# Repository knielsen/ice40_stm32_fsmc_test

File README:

Small test of fast communication between STM32F4 and ICE40 using the STM32 FSMC.

Pinout for the FSMC (this for plugged into the J3 slot):

  func  STM32  ICE40
  A0    PF0    R4
  A1    PF1    R3
  D0	PD14   N10
  D1	PD15   M11
  D2	PD0    T16
  NE2	PG9    N12
  NOE	PD4    T13
  NWE	PD5    P13

The external clock for the ICE40 is on J3. A test pin PB11 on the
STM32F4 is connected to R16 on the ICE40. A serial Tx out from STM32
can be connected from PB10 on the STM32F4 board to T15 on the ICE40
(will be proxied to the FTDI on the ICE40 breakout board).

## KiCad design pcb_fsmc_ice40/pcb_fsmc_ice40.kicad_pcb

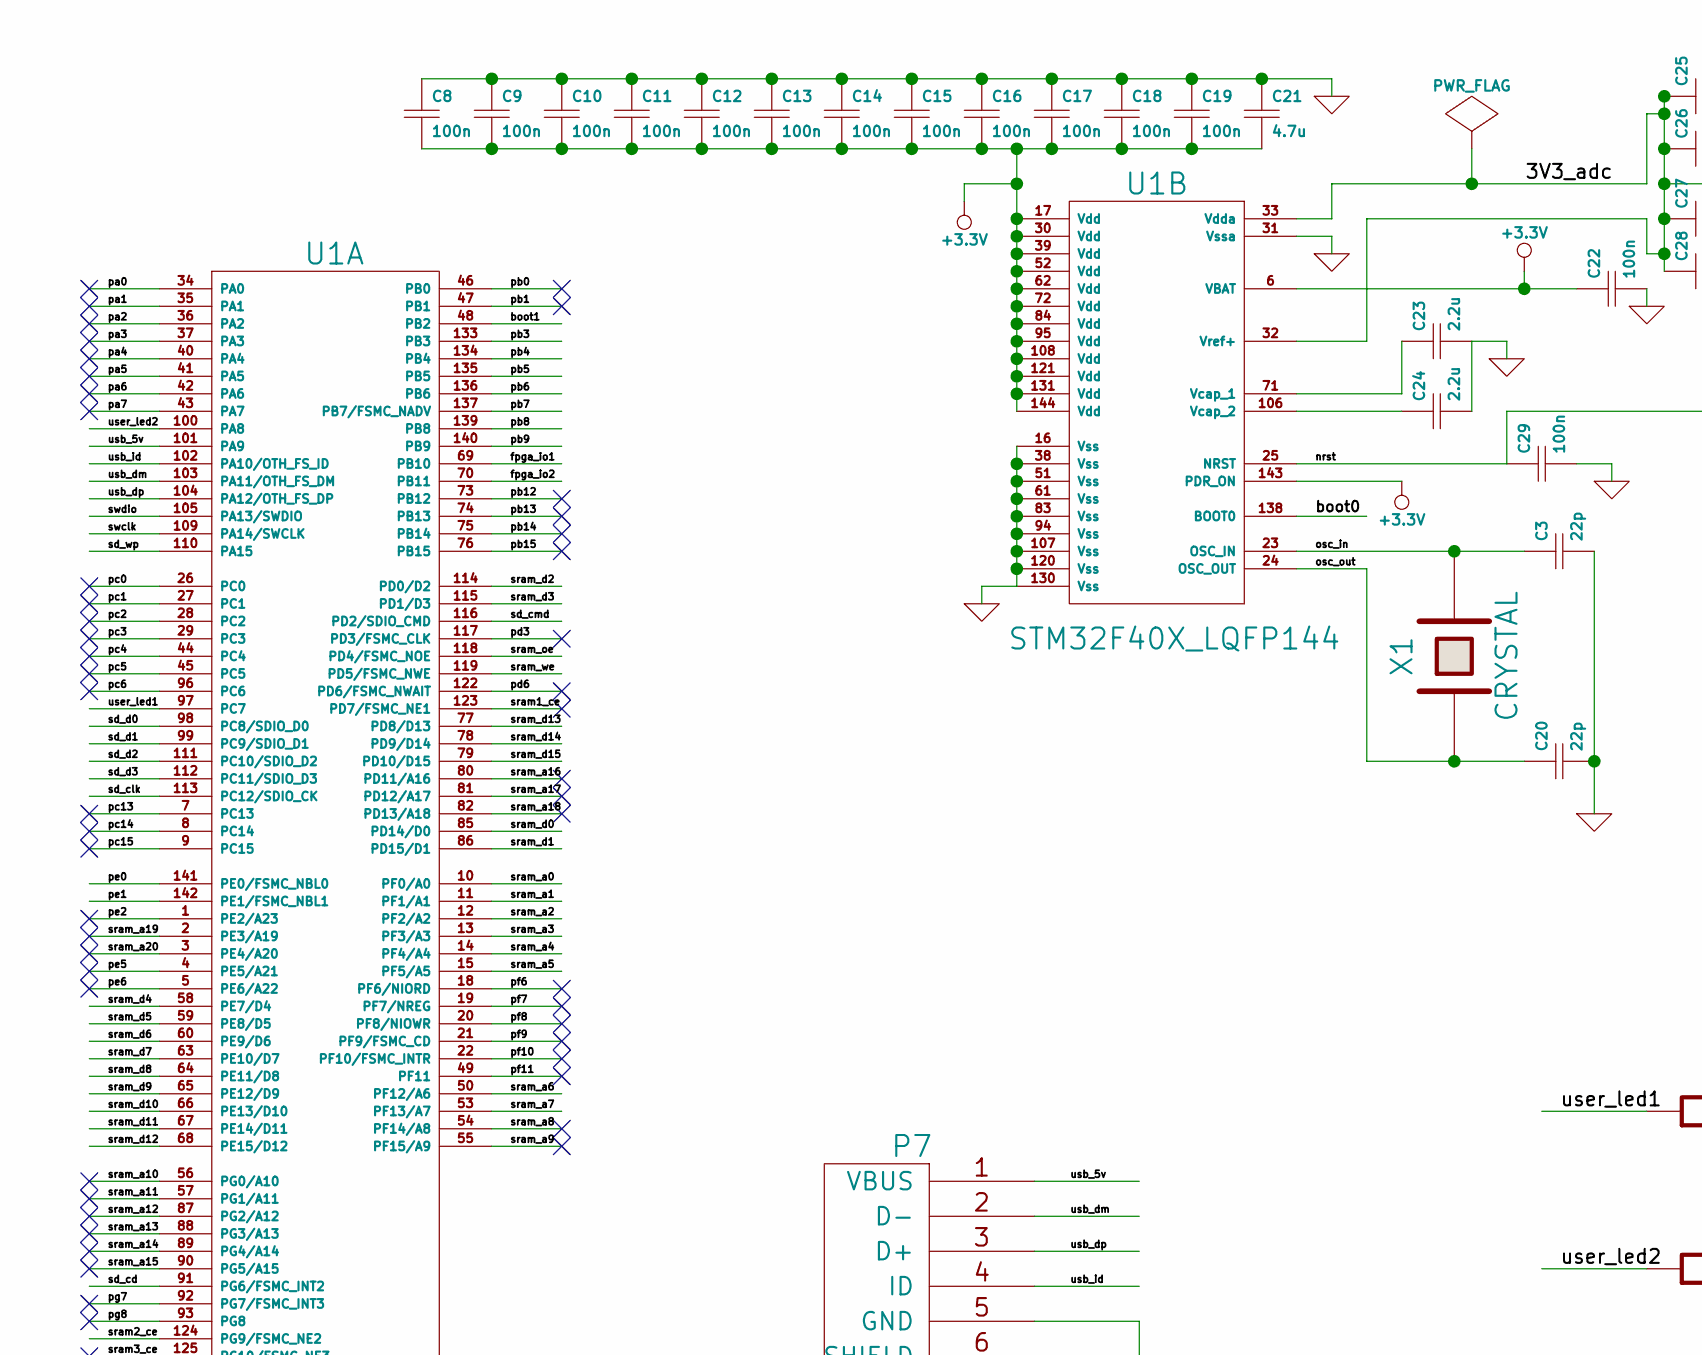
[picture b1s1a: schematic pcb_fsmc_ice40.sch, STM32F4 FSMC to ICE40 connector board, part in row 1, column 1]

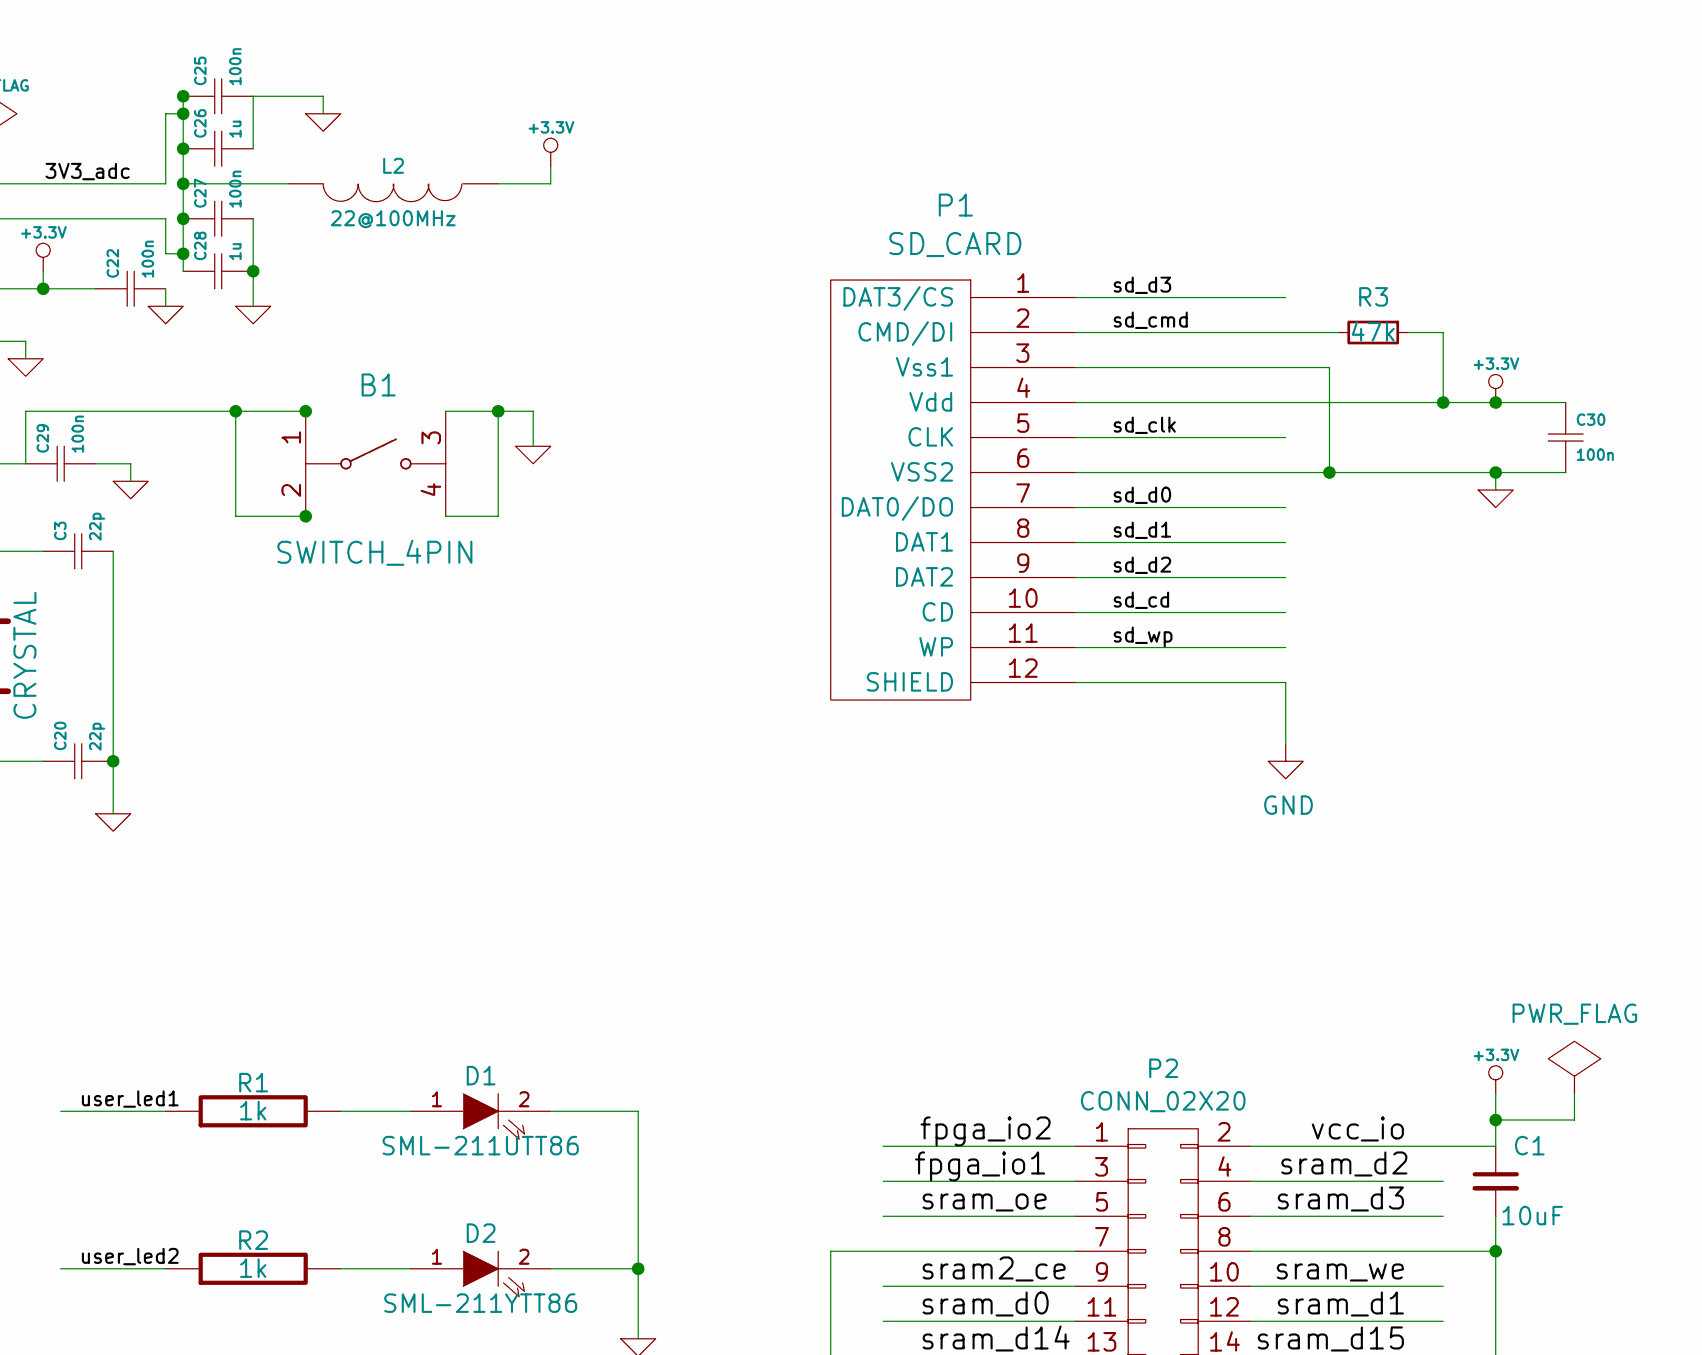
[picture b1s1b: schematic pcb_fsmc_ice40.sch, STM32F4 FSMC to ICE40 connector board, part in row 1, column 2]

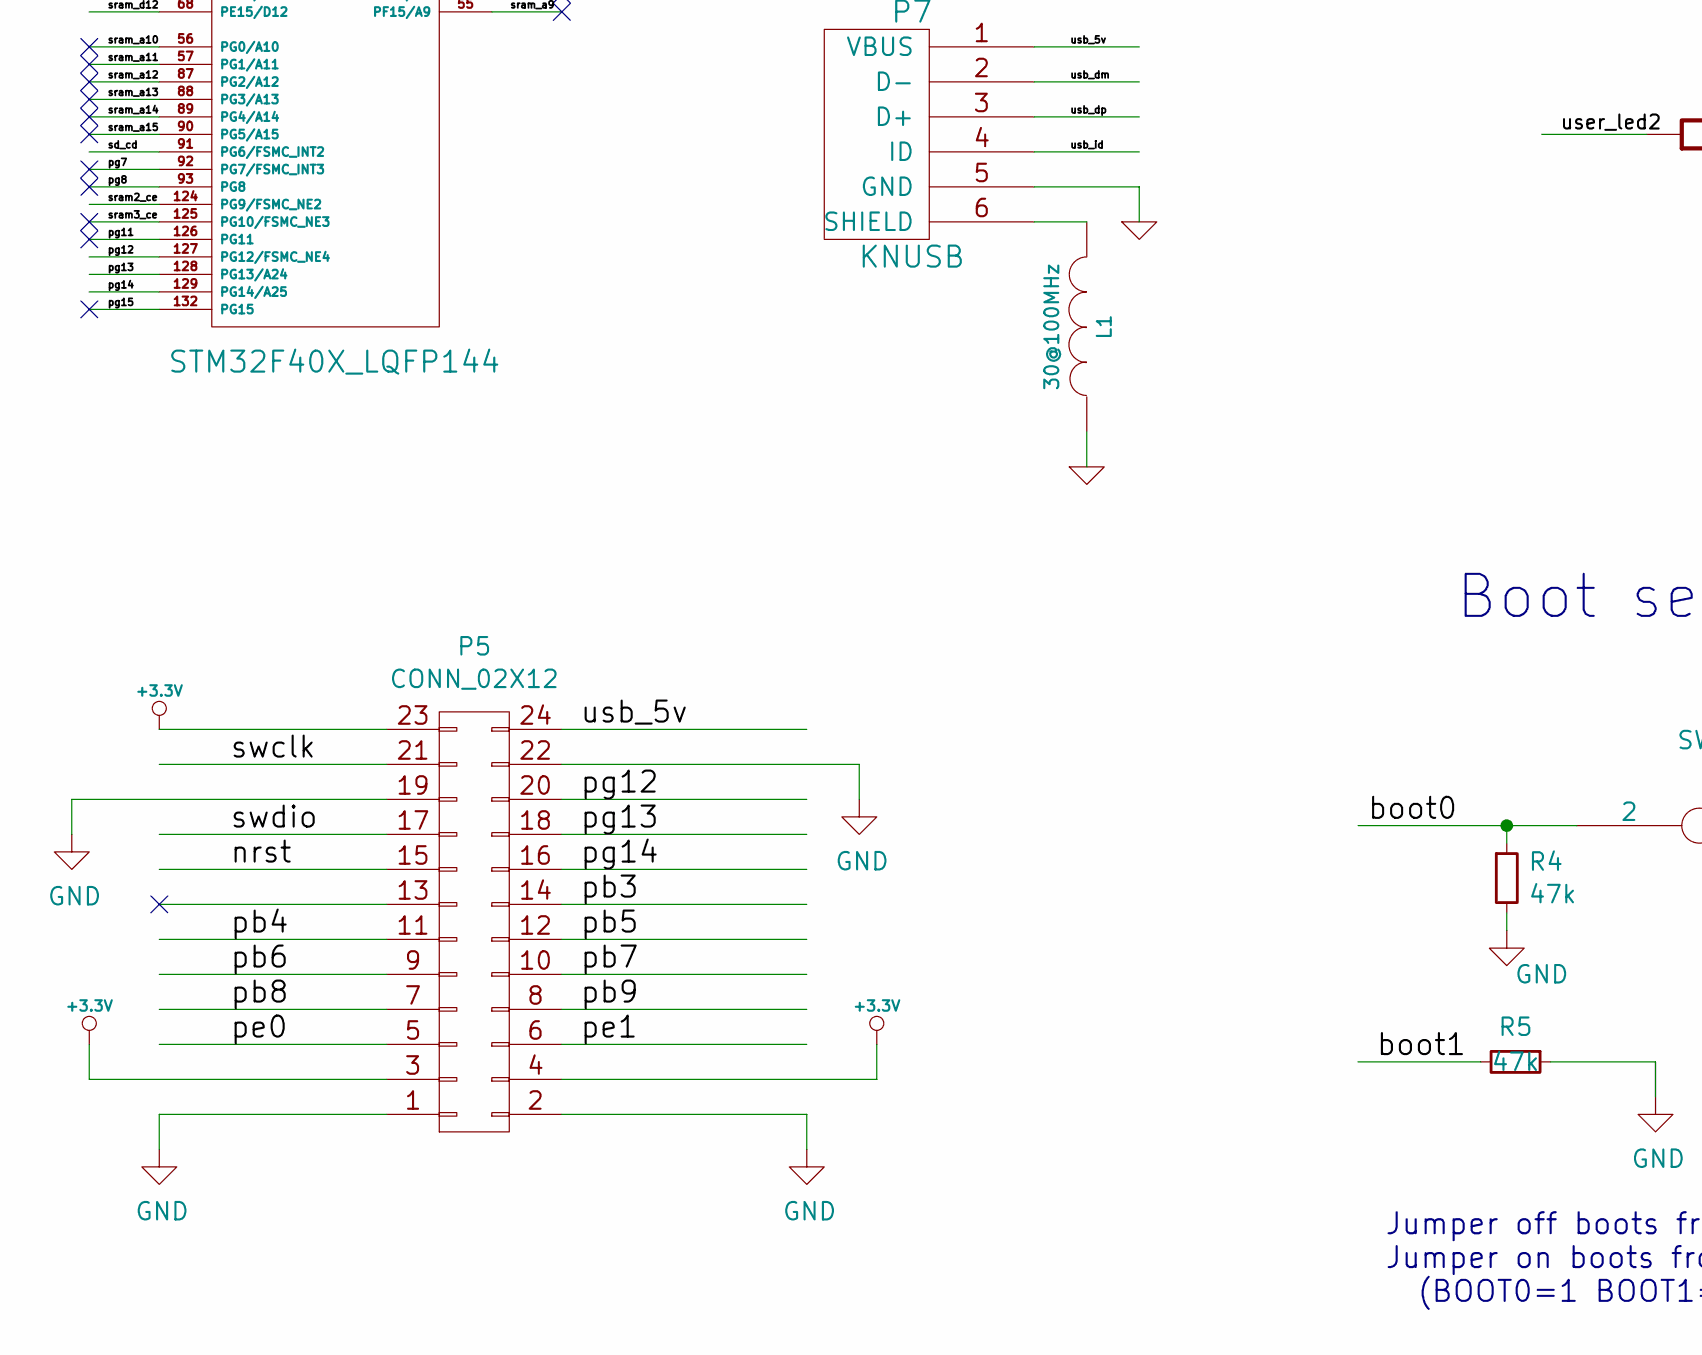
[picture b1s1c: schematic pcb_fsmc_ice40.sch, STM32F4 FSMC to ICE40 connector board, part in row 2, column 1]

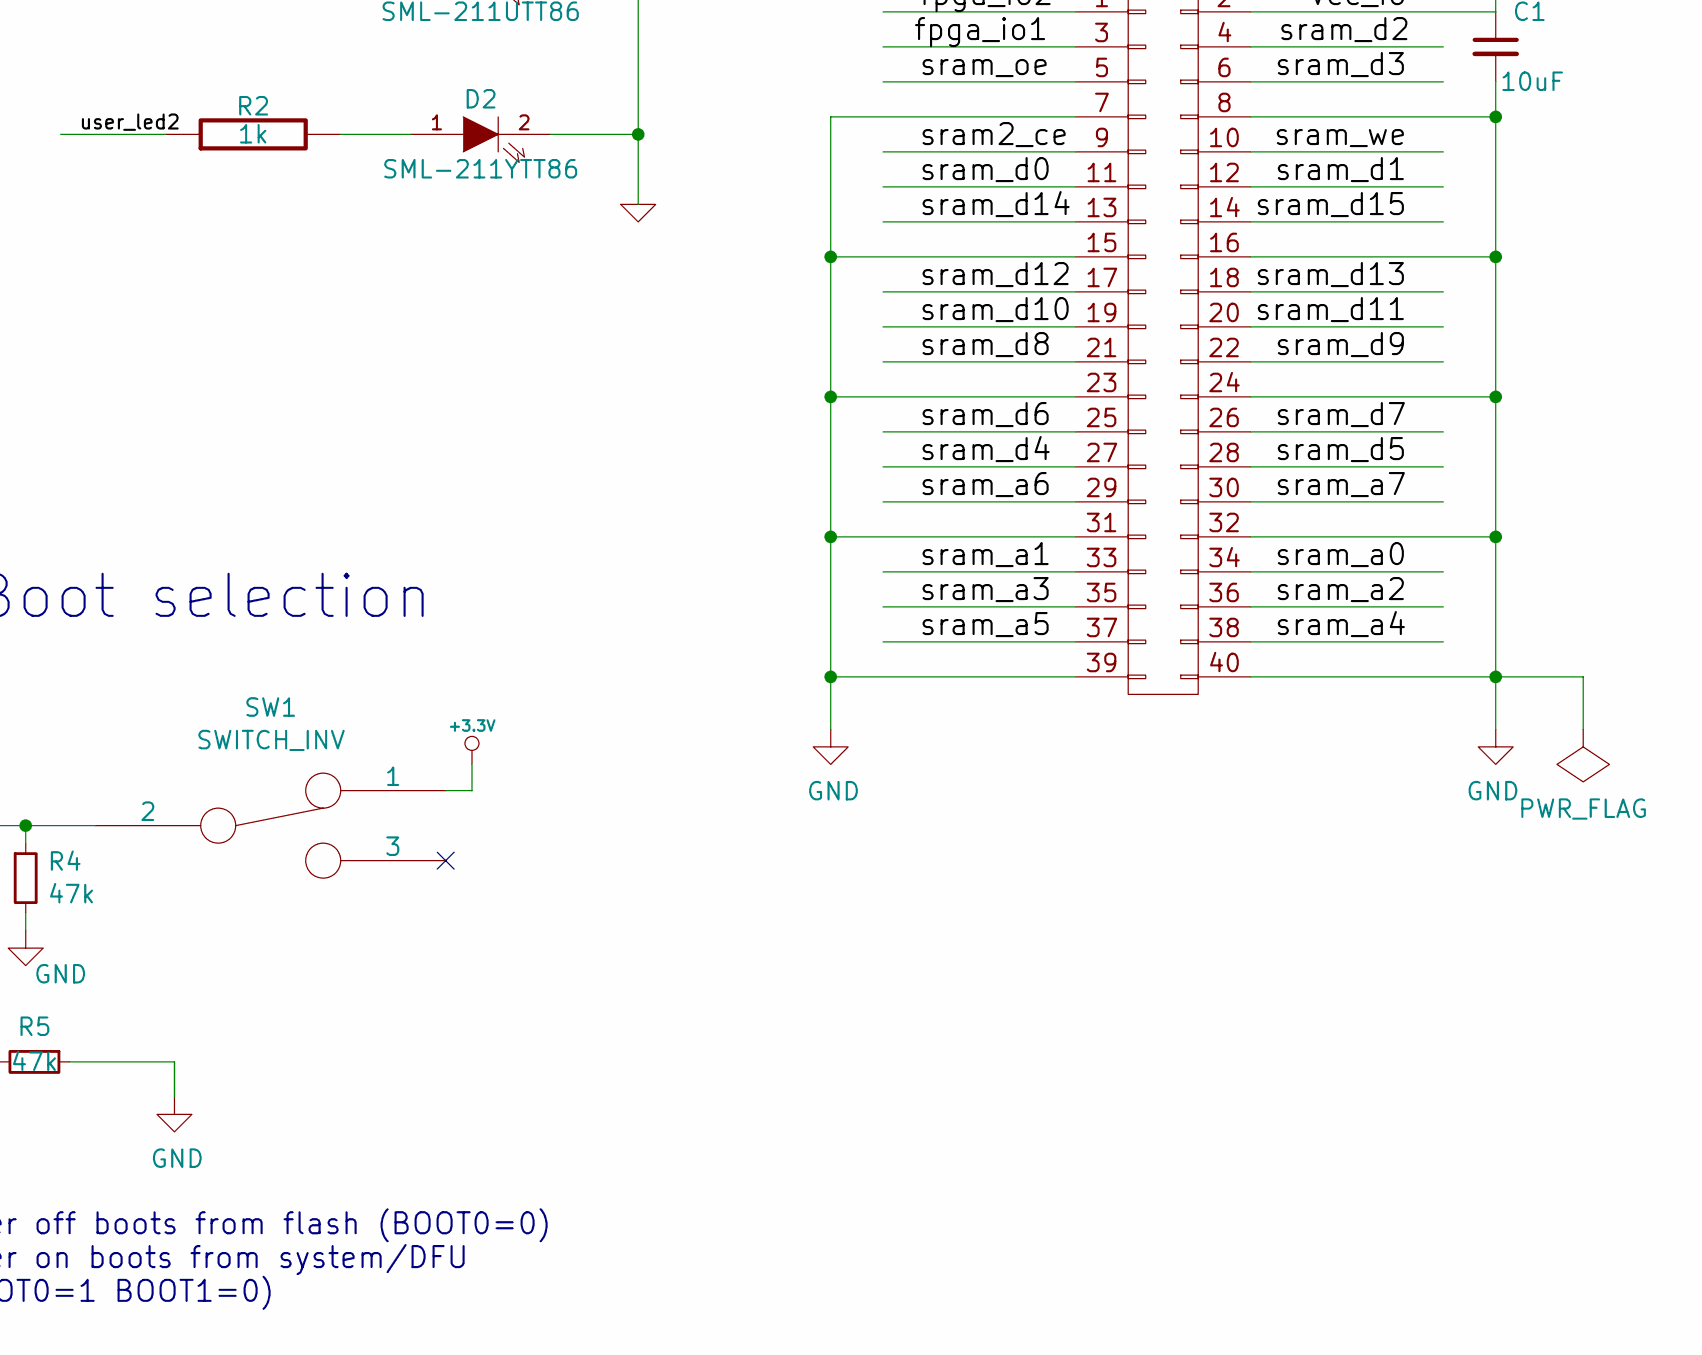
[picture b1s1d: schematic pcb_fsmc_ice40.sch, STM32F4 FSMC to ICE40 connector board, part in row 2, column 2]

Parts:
B1: SWITCH_4PIN; pushbutton_EVQ_PSR02K
C1: 10uF; C_0805
C3, C20: 22p; C_0603
C8, C9, C10, C11, C12, C13, C14, C15, C16, C17, C18, C19, C22, C25, C27, C29, C30: 100n; C_0603
C21: 4.7u; C_0603
C23, C24: 2.2u; C_0603
C26, C28: 1u; C_0603
D1: SML-211UTT86; LED_0603
D2: SML-211YTT86; LED_0603
L1: 30@100MHz; C_0603
L2: 22@100MHz; C_0603
P1: SD_CARD; SD_CARD_10100
P2: CONN_02X20; ice40_vert_conn
P5: CONN_02X12; ice40_top_conn_12
P7: KNUSB; 10103594-0001LF
R1, R2: 1k; R_0603
R3, R4, R5: 47k; R_0603
SW1: SWITCH_INV; switch_msk_12c02
U1: STM32F40X_LQFP144; LQFP-144_20x20mm_Pitch0.5mm
X1: CRYSTAL; 2-SOJ

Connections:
+3.3V: C1.1, C8.2, C9.2, C10.2, C11.2, C12.2, C13.2, C14.2, C15.2, C16.2, C17.2, C18.2, C19.2, C21.2, C22.1, C30.1, L2.1, P1.4 (Vdd), P2.2, P5.3, P5.4, P5.23, R3.1, SW1.1, U1.6 (VBAT), U1.17 (Vdd), U1.30 (Vdd), U1.39 (Vdd), U1.52 (Vdd), U1.62 (Vdd), U1.72 (Vdd), U1.84 (Vdd), U1.95 (Vdd), U1.108 (Vdd), U1.121 (Vdd), U1.131 (Vdd), U1.143 (PDR_ON), U1.144 (Vdd)
/3V3_adc: C25.1, C26.1, C27.1, C28.1, L2.2, U1.32 (Vref+), U1.33 (Vdda)
/boot0: R4.1, SW1.2, U1.138 (BOOT0)
/boot1: R5.2, U1.48 (PB2)
/fpga_io1: P2.3, U1.69 (PB10)
/fpga_io2: P2.1, U1.70 (PB11)
/nrst: B1.1, B1.2, C29.1, P5.15, U1.25 (NRST)
/osc_in: C3.1, U1.23 (OSC_IN), X1.2
/osc_out: C20.1, U1.24 (OSC_OUT), X1.1
/pa0: U1.34 (PA0)
/pa1: U1.35 (PA1)
/pa2: U1.36 (PA2)
/pa3: U1.37 (PA3)
/pa4: U1.40 (PA4)
/pa5: U1.41 (PA5)
/pa6: U1.42 (PA6)
/pa7: U1.43 (PA7)
/pb0: U1.46 (PB0)
/pb1: U1.47 (PB1)
/pb3: P5.14, U1.133 (PB3)
/pb4: P5.11, U1.134 (PB4)
/pb5: P5.12, U1.135 (PB5)
/pb6: P5.9, U1.136 (PB6)
/pb7: P5.10, U1.137 (PB7/FSMC_NADV)
/pb8: P5.7, U1.139 (PB8)
/pb9: P5.8, U1.140 (PB9)
/pb12: U1.73 (PB12)
/pb13: U1.74 (PB13)
/pb14: U1.75 (PB14)
/pb15: U1.76 (PB15)
/pc0: U1.26 (PC0)
/pc1: U1.27 (PC1)
/pc2: U1.28 (PC2)
/pc3: U1.29 (PC3)
/pc4: U1.44 (PC4)
/pc5: U1.45 (PC5)
/pc6: U1.96 (PC6)
/pc13: U1.7 (PC13)
/pc14: U1.8 (PC14)
/pc15: U1.9 (PC15)
/pd3: U1.117 (PD3/FSMC_CLK)
/pd6: U1.122 (PD6/FSMC_NWAIT)
/pe0: P5.5, U1.141 (PE0/FSMC_NBL0)
/pe1: P5.6, U1.142 (PE1/FSMC_NBL1)
/pe2: U1.1 (PE2/A23)
/pe5: U1.4 (PE5/A21)
/pe6: U1.5 (PE6/A22)
/pf6: U1.18 (PF6/NIORD)
/pf7: U1.19 (PF7/NREG)
/pf8: U1.20 (PF8/NIOWR)
/pf9: U1.21 (PF9/FSMC_CD)
/pf10: U1.22 (PF10/FSMC_INTR)
/pf11: U1.49 (PF11)
/pg7: U1.92 (PG7/FSMC_INT3)
/pg8: U1.93 (PG8)
/pg11: U1.126 (PG11)
/pg12: P5.20, U1.127 (PG12/FSMC_NE4)
/pg13: P5.18, U1.128 (PG13/A24)
/pg14: P5.16, U1.129 (PG14/A25)
/pg15: U1.132 (PG15)
/sd_cd: P1.10 (CD), U1.91 (PG6/FSMC_INT2)
/sd_clk: P1.5 (CLK), U1.113 (PC12/SDIO_CK)
/sd_cmd: P1.2 (CMD/DI), R3.2, U1.116 (PD2/SDIO_CMD)
/sd_d0: P1.7 (DAT0/DO), U1.98 (PC8/SDIO_D0)
/sd_d1: P1.8 (DAT1), U1.99 (PC9/SDIO_D1)
/sd_d2: P1.9 (DAT2), U1.111 (PC10/SDIO_D2)
/sd_d3: P1.1 (DAT3/CS), U1.112 (PC11/SDIO_D3)
/sd_wp: P1.11 (WP), U1.110 (PA15)
/sram1_ce: U1.123 (PD7/FSMC_NE1)
/sram2_ce: P2.9, U1.124 (PG9/FSMC_NE2)
/sram3_ce: U1.125 (PG10/FSMC_NE3)
/sram_a0: P2.34, U1.10 (PF0/A0)
/sram_a1: P2.33, U1.11 (PF1/A1)
/sram_a2: P2.36, U1.12 (PF2/A2)
/sram_a3: P2.35, U1.13 (PF3/A3)
/sram_a4: P2.38, U1.14 (PF4/A4)
/sram_a5: P2.37, U1.15 (PF5/A5)
/sram_a6: P2.29, U1.50 (PF12/A6)
/sram_a7: P2.30, U1.53 (PF13/A7)
/sram_a8: U1.54 (PF14/A8)
/sram_a9: U1.55 (PF15/A9)
/sram_a10: U1.56 (PG0/A10)
/sram_a11: U1.57 (PG1/A11)
/sram_a12: U1.87 (PG2/A12)
/sram_a13: U1.88 (PG3/A13)
/sram_a14: U1.89 (PG4/A14)
/sram_a15: U1.90 (PG5/A15)
/sram_a16: U1.80 (PD11/A16)
/sram_a17: U1.81 (PD12/A17)
/sram_a18: U1.82 (PD13/A18)
/sram_a19: U1.2 (PE3/A19)
/sram_a20: U1.3 (PE4/A20)
/sram_d0: P2.11, U1.85 (PD14/D0)
/sram_d1: P2.12, U1.86 (PD15/D1)
/sram_d2: P2.4, U1.114 (PD0/D2)
/sram_d3: P2.6, U1.115 (PD1/D3)
/sram_d4: P2.27, U1.58 (PE7/D4)
/sram_d5: P2.28, U1.59 (PE8/D5)
/sram_d6: P2.25, U1.60 (PE9/D6)
/sram_d7: P2.26, U1.63 (PE10/D7)
/sram_d8: P2.21, U1.64 (PE11/D8)
/sram_d9: P2.22, U1.65 (PE12/D9)
/sram_d10: P2.19, U1.66 (PE13/D10)
/sram_d11: P2.20, U1.67 (PE14/D11)
/sram_d12: P2.17, U1.68 (PE15/D12)
/sram_d13: P2.18, U1.77 (PD8/D13)
/sram_d14: P2.13, U1.78 (PD9/D14)
/sram_d15: P2.14, U1.79 (PD10/D15)
/sram_oe: P2.5, U1.118 (PD4/FSMC_NOE)
/sram_we: P2.10, U1.119 (PD5/FSMC_NWE)
/swclk: P5.21, U1.109 (PA14/SWCLK)
/swdio: P5.17, U1.105 (PA13/SWDIO)
/usb_5v: P5.24, P7.1 (VBUS), U1.101 (PA9)
/usb_dm: P7.2 (D-), U1.103 (PA11/OTH_FS_DM)
/usb_dp: P7.3 (D+), U1.104 (PA12/OTH_FS_DP)
/usb_id: P7.4 (ID), U1.102 (PA10/OTH_FS_ID)
/user_led1: R1.1, U1.97 (PC7)
/user_led2: R2.1, U1.100 (PA8)
GND: B1.3, B1.4, C1.2, C3.2, C8.1, C9.1, C10.1, C11.1, C12.1, C13.1, C14.1, C15.1, C16.1, C17.1, C18.1, C19.1, C20.2, C21.1, C22.2, C23.2, C24.2, C25.2, C26.2, C27.2, C28.2, C29.2, C30.2, D1.2 (K), D2.2 (K), L1.1, P1.3 (Vss1), P1.6 (VSS2), P1.12 (SHIELD), P2.7, P2.8, P2.15, P2.16, P2.23, P2.24, P2.31, P2.32, P2.39, P2.40, P5.1, P5.2, P5.19, P5.22, P7.5 (GND), R4.2, R5.1, U1.16 (Vss), U1.31 (Vssa), U1.38 (Vss), U1.51 (Vss), U1.61 (Vss), U1.83 (Vss), U1.94 (Vss), U1.107 (Vss), U1.120 (Vss), U1.130 (Vss)
unnamed: C23.1, U1.71 (Vcap_1)
unnamed: C24.1, U1.106 (Vcap_2)
unnamed: D1.1 (A), R1.2
unnamed: D2.1 (A), R2.2
unnamed: L1.2, P7.6 (SHIELD)

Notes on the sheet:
Boot selection
Jumper off boots from flash (BOOT0=0) Jumper on boots from system/DFU (BOOT0=1 BOOT1=0)

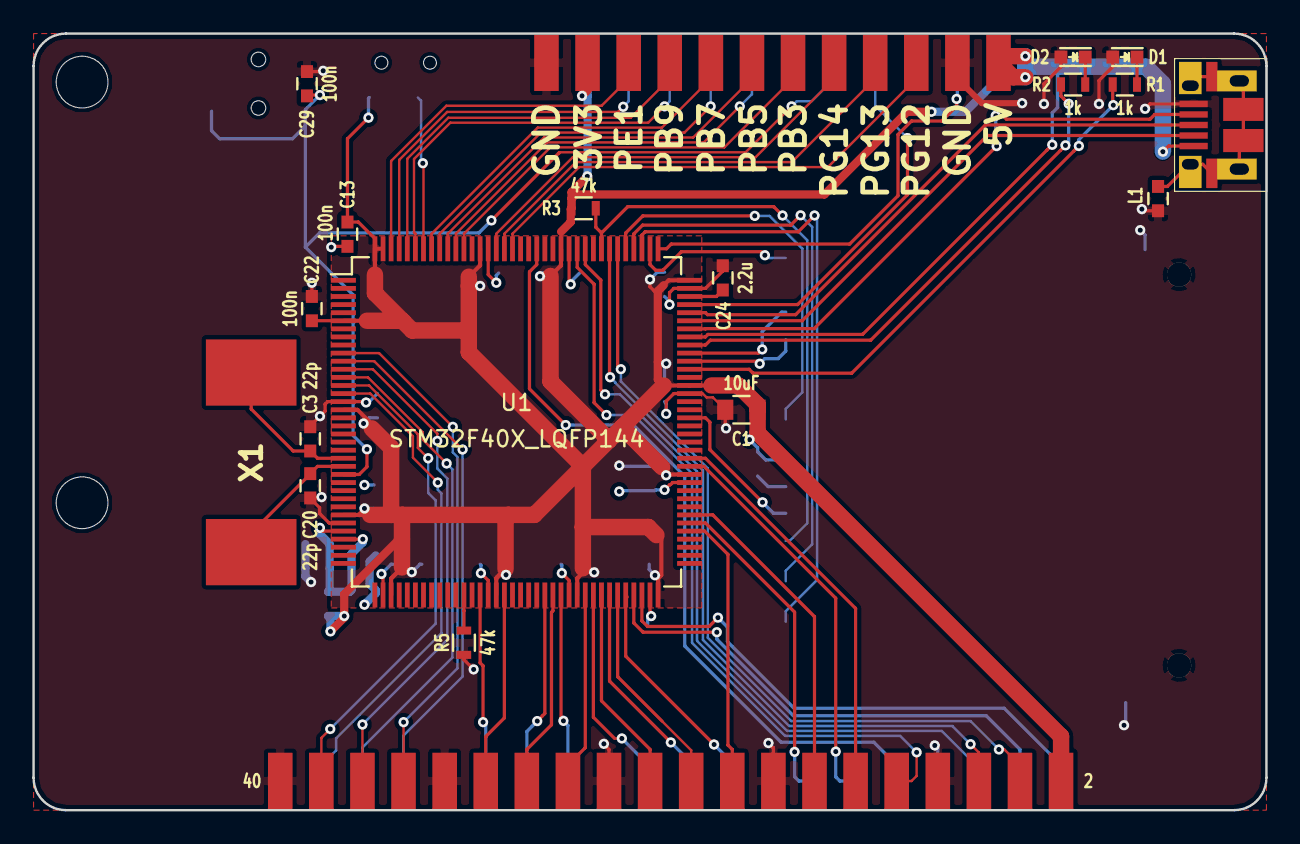
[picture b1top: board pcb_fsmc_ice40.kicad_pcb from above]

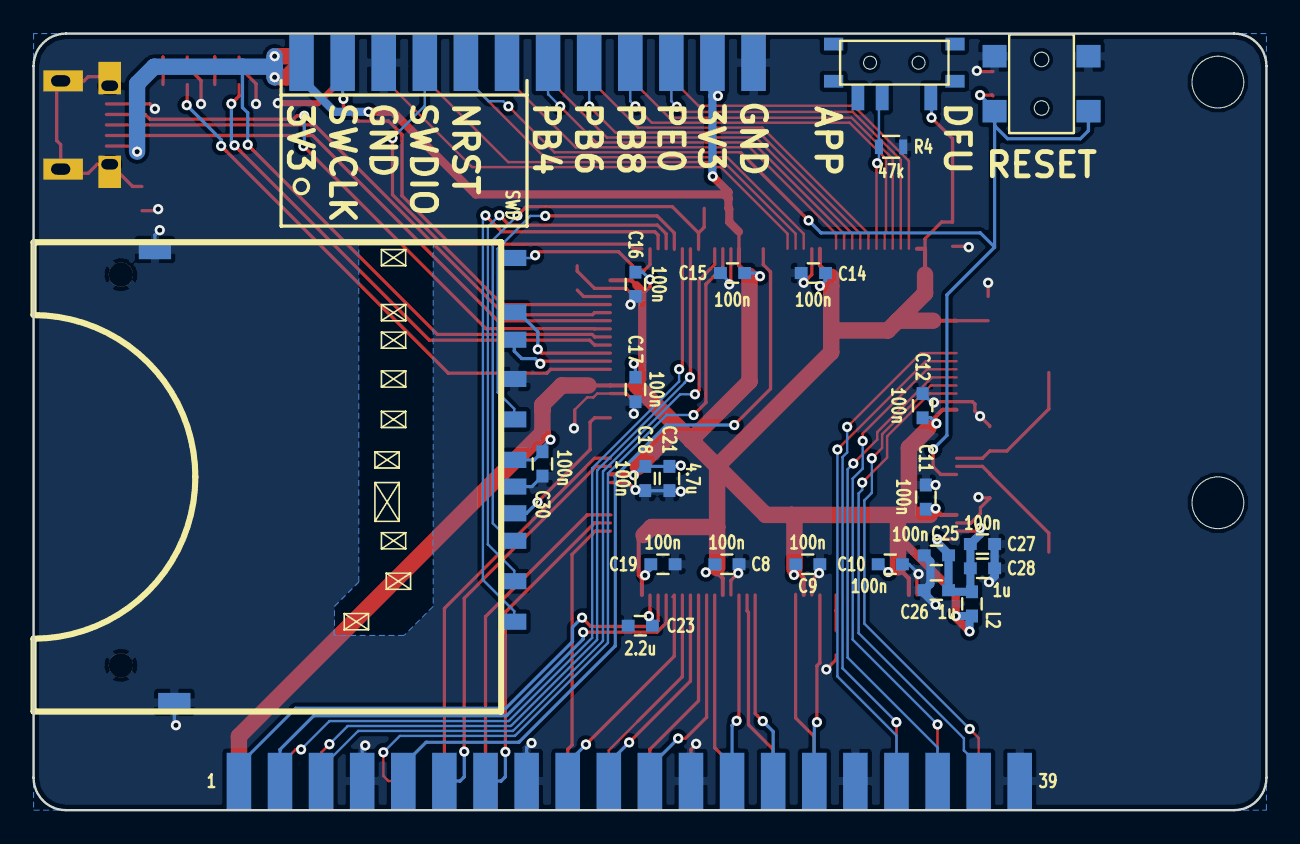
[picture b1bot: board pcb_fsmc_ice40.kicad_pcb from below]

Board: 2 copper layers, 76.2 x 48.0 mm, 42 parts (23 on the bottom side), 70 nets.

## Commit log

2016-07-29 First step towards talking between STM32 and ICE40.
    In this commit, the STM32F4 MCU outputs a simple pulse (at around 2Hz)
    on a pin. The ICE40 reads the pin, synchronises to its own clock
    domain, detects and counts positive edges on the input, and displays
    an 8-bit counter value on the 8 LEDs on the hx8k breakout board.
2016-07-29 Enable FSMC SRAM2.
    Now we can count NE2 (chip enable) pulses on the ICE40 generated from
    writes to the FSMC on the STM32.
2016-07-29 First working (somewhat) FSMC interface between STM32 and ICE40.
    Two registers are defined, at address 0x0 and 0x2 (first and second
    16-bit word). The first bit in each address each controls a LED on the
    ICE40 board.
    Only write so far, no read.
    Doesn't work reliably. It works after flashing the STM32, but then a
    reset breaks it until next flash, somehow the NOE and NWE pins stop
2016-07-30 Add a simple README with pinouts.
2016-07-30 Fix timing bug that caused STM32-side to fail after reset.
    The problem was in the STM32-generated initialisation code. It
    enables GPIOD and then immediately after configures the alternate
    functions for that GPIO. Depending on compiler internals (and
    apparently reset method), this can happen so quickly after one another
    that the GPIOD has not yet started before the access to alternate
    function config register, leaving 4 GPIOD pins not configured
2016-07-31 Partial work towards a STM32 daughterboard for ICE40 breakout board.
2016-07-31 Some more work on PCB, still work left to do.
2016-08-02 Some routing changes.
2016-08-03 Mostly complete routing.
2016-08-03 Mostly complete routing now.
2016-08-04 New implementation of FSMC interface FPGA-side.
    This is a clocked interface. It is intended to be better at avoiding
    glitches due to sync errors, for example missing the NE pulse in
    closely spaced back-to-back transactions.
    Also implements reading registers from the FPGA, this is however still
    untested...
2016-08-04 Proxy a serial debug from the STM32F4 through the ICE40 to the FTDI.
    This is a nice trick for getting debug output out of the STM32F4,
    without the need for a separate usb-to-serial converter.
2016-08-04 Move the extra IO fpga_io1 and fpga_io2 to PB10/PB11.
    These have USART Rx/Tx available, so we can use these two spare IOs
    with the trick wher ethe FPGA proxies the UART signal from STM32 to
    the FTDI chip on the ICE40 board, simplifying serial debugging.
2016-08-04 Add forgotten no-connect symbol.
2016-08-04 Working FSMC read from FPGA.
    Adjust read timing to make things work. DataSetupTime needed to be increased
    by one, to 7 - data setup time and bus turnaround time could though be
    reduced by 4 total both to zeros.
2016-08-04 Implement 3-bit databus (tested).
    Had to decrease FSMC speed a bit more to avoid glitches. Maybe the
    nest-of-jumper-wires has influence here as well, might be a noise
    problem?
2016-08-04 Parameter for databus width.
2016-08-04 Implement a two-bit address bus (tested).
2016-08-05 Fix a small logic bug.
2016-08-05 Adjust timing according to timing diagram drawn on paper.
2016-08-05 Add info about serial debug pinout.
2016-08-07 Some steps towards debugging FSMC unreliability.
2016-08-08 Avoid using arrays completely, for now.
    Not sure I understand exactly how those work in verilog (or in yosys).
2016-08-08 Some more tests, and relaxed timing for now...
2016-08-08 Small output tweak.
2016-08-08 New test, read-only.
    Read out counters that increment on each read.
    Shows occasional glitches, but not yet clear exactly how...
2016-08-09 Zero out registers at start of test, to better spot glitches...
2016-08-11 Connect PA9 to usb_5v, as used by some ST library code.
2016-08-11 Minor tweaks.
2016-08-11 Silk screen addition.
2016-08-26 New write-only test of FSMC interface to ICE40 FPGA.
2016-08-31 Go down to 150 MHz (from 172 MHz) to get reliable write.
2016-10-11 Split read/write adr, and a bit slower timing
2016-10-12 Changes to work with new plugin board for ICE40.
    Use new StdPeriph library - old HSE timeout default is too low for the
    board for some reason.
    Halt in case of HSE startup failure, for easier detection of the problem.
    Change pin mapping to work with the STM3F4 plugin board in slot J3.
    Change LED and USART pins.
2016-10-13 Add commented-out code for second LED.
2016-10-31 16b/8b data/addr bus
2016-10-31 initial vga support
2016-11-04 Fix typo for vga clock
2016-11-04 Add a simple font
    To replace the original that was forgotten in git add.
2016-11-04 Comment on PLL clock
2016-11-04 Simple scroll-text to test the VGA module over FSMC.
2016-11-04 Add dfu programming target (untested)
2016-11-07 Add missing dependencies.
2016-11-07 Move to full 160x64 char buffer.
2016-11-07 Full charbuffer accessible from STM32.
    Register 0 sets the charbuffer index for subsequent data write to register 1.
2016-11-07 Implement auto-incrementing charbuf write register
2016-11-07 Fix autoincrement charbuf write.
    Now it does proper post-increment (before it was incrementing one
    cycle too early, effectively doing pre-increment).
2016-11-08 Fix off-by-one error in charbuffer size.
2016-11-08 Minor stuffs.
2016-11-08 Buffer output signals for consistent edge times.
